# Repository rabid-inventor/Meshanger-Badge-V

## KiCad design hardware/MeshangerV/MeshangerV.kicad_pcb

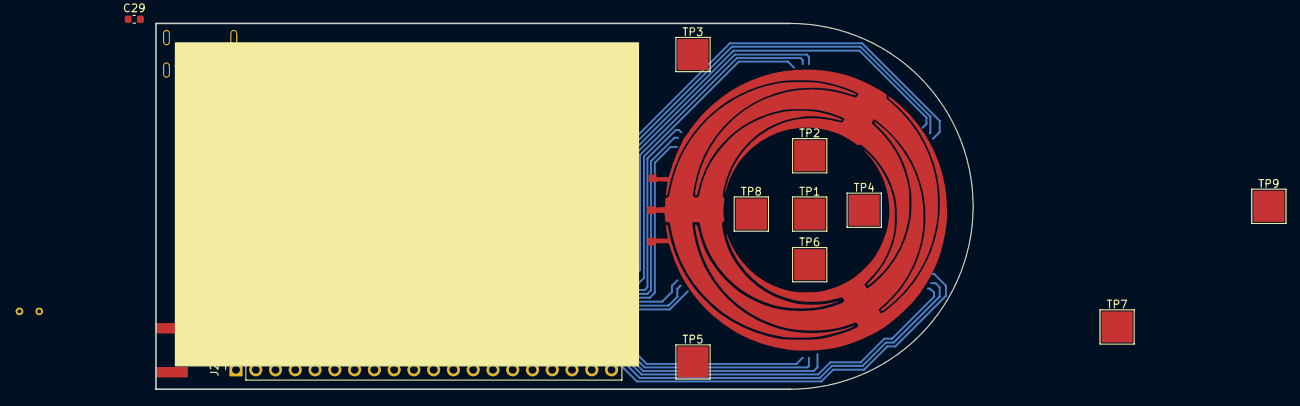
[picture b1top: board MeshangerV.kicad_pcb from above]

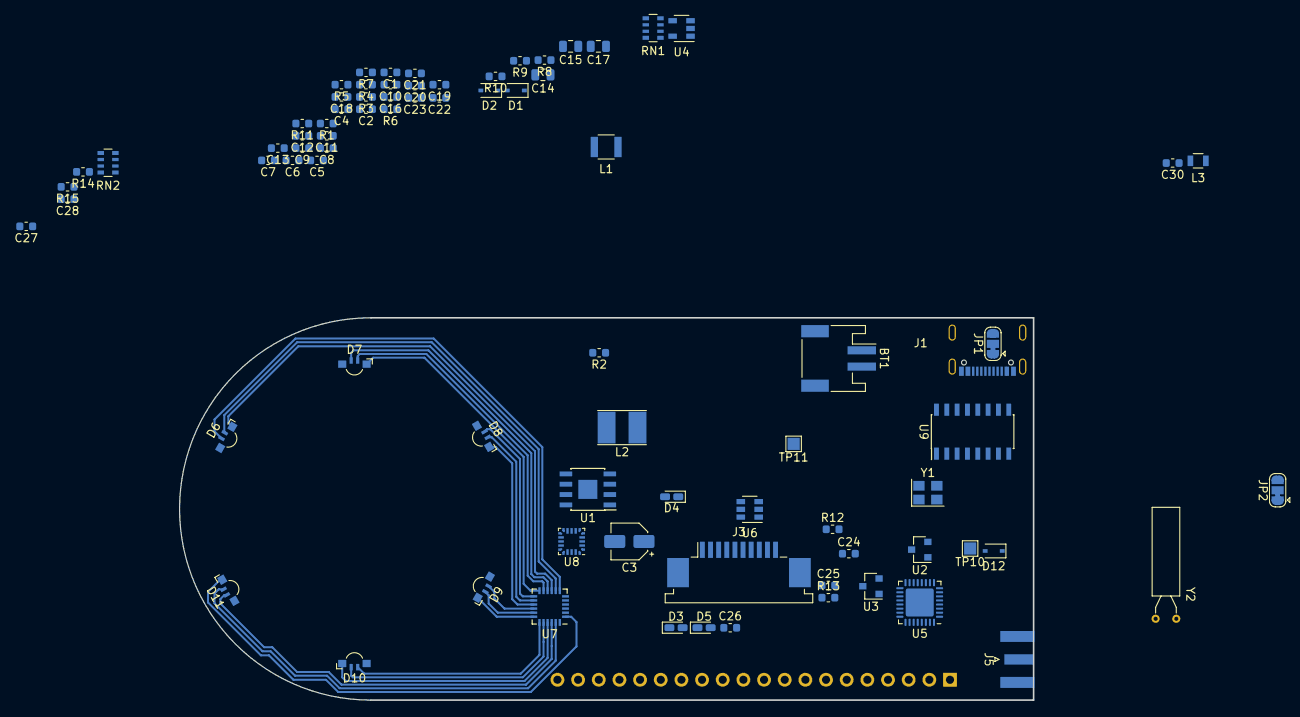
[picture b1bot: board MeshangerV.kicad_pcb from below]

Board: 2 copper layers, 105.0 x 47.0 mm, 92 parts (80 on the bottom side), 78 nets.

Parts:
BT1: Battery_Cell; JST_PH_S2B-PH-SM4-TB_02x2.00mm_Angled
C1, C2, C4, C5, C6, C7, C9, C11, C12, C13, C16, C18, C19, C20, C21, C22, C23, C24, C25, C26, C27, C28, C29, C30: C_Small; C_0603_1608Metric
C3: CP; CP_Elec_4x4.5
C8, C10: 1uF; C_0603_1608Metric
C14, C15: 22uF; C_0805_2012Metric
C17: 10uF; C_0805_2012Metric
D1, D2, D12: D_Schottky; D_SOD-323
D3, D4, D5: LED; LED_0603_1608Metric_Castellated
D6, D7, D8, D9, D10, D11: LED_RABG; LED_Kingbright_APFA3010_3x1.5mm_Horizontal
J1: USB_C_Receptacle_USB2.0; VACON_CSP_USC16_TR
J2: Conn_01x20_Male; PinSocket_1x20_P2.54mm_Vertical
J3: Conn_01x10_MountingPin; TE_1-84952-0_1x10-1MP_P1.0mm_Horizontal
J4: Conn_01x03; touchwheel
J5: Conn_Coaxial; SMA_Samtec_SMA-J-P-H-ST-EM1_EdgeMount
JP1, JP2: SolderJumper_3_Bridged12; SolderJumper-3_P1.3mm_Bridged12_RoundedPad1.0x1.5mm
L1: L_Small; L_1210
L2: L_Small; L_Taiyo-Yuden_NR-40xx_HandSoldering
L3: L_Small; L_0805
R1, R2, R3, R4, R5, R6, R7, R8, R9, R10, R11, R12, R13, R14, R15: R_Small; R_0603_1608Metric
RN1, RN2: R_Pack04; R_Array_Convex_4x0603
TP1, TP2, TP3, TP4, TP5, TP6, TP7, TP8, TP9: TestPoint; TestPoint_Pad_4.0x4.0mm
TP10: CH_BL_SEL; TestPoint_Pad_1.5x1.5mm
TP11: PROGVCC; TestPoint_Pad_1.5x1.5mm
U1: TP4056; SOIC-8-1EP_3.9x4.9mm_P1.27mm_EP2.35x2.35mm
U2, U3: AP7333-33SRG-7; SOT-23
U4: AP3012KTR-G1; SOT-23-5
U5: ESP32-C3; QFN-32-1EP_5x5mm_P0.5mm_EP3.45x3.45mm
U6: AP2502KTR-G1; SOT-23-6
U7: SN3218; QFN-24_4x4mm_Pitch0.5mm
U8: AT42QT2120; ST_UFQFPN-20_3x3mm_Pitch0.5mm
U9: CH552G; SOIC-16_3.9x9.9mm_P1.27mm
Y1: 40MHz; Crystal_SMD_Abracon_ABM8G-4Pin_3.2x2.5mm
Y2: 32k; Crystal_AT310_D3.0mm_L10.0mm_Horizontal

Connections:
+3.3VA: C10.1, C14.1, C16.1, C19.1, C22.1, J2.18, U3.2, U5.2, U5.3, U5.31, U5.32
+3V3: C3.1, C4.1, C5.1, C7.1, C8.1, C9.1, C11.1, C15.1, C17.1, C20.1, C23.1, C24.1, C27.1, C28.1, D1.1, D2.1, D3.2, D4.2, D5.2, D6.2, D7.2, D8.2, D9.2, D10.2, D11.2, D12.2, J2.17, J2.19, J3.5, R11.1, R12.1, R15.1, RN1.6, RN1.7, RN1.8, RN2.5, RN2.6, RN2.7, RN2.8, U2.2, U2.3, U3.3, U5.11, U5.17, U7.3, U8.9, U9.16
/ANT: C29.1, L3.1, U5.1
/BLSEL: J2.9, J3.8, U5.15, U9.3
/BVOLT: J2.16, R7.2, R8.1, U5.6
/CC1: J1.A5, R5.2
/CC2: J1.B5, R4.2
/CHRG_SD: R6.2, U1.8
/CHUSB+: JP2.1, TP10.1, U9.12
/CHUSB-: JP1.1, U9.13
/Display hardware/RES: J3.9, R12.2
/Display hardware/V0: C25.1, J3.3
/Display hardware/VG: C26.1, J3.1
/Display hardware/XV0: C25.2, J3.2
/ESPUSB+: J2.6, JP2.3, U5.26
/ESPUSB-: J2.5, JP1.3, U5.25
/ESP_ENABLE: R11.2, U5.7, U9.2
/ESP_RX: J2.3, U5.27, U9.7
/ESP_TX: J2.4, U5.28, U9.8
/INPUTINT: J2.10, J3.10, RN1.1, RN2.3, U5.14, U8.15
/LCD_BL_EN: J2.8, R13.1, RN1.4, U5.16, U6.1
/LED_SD: RN2.4, U7.24
/MISO: J2.12, U5.10
/MOSI: J2.13, J3.6, U5.12
/SCK: J2.11, J3.7, U5.13
/SCL: J2.14, RN2.2, U5.9, U8.14, U9.4
/SDA: J2.15, RN2.1, U5.8, U7.5, U7.6, U8.11, U9.5
/V_BAT: BT1.1, C2.1, C6.1, L2.2, R7.1, U1.5, U4.5
/_CHRG: U1.7, U9.10
/_STDBY: U1.6, U9.9
/control hardware/1B: D6.3, U7.7
/control hardware/1G: D6.4, U7.8
/control hardware/1R: D6.1, U7.9
/control hardware/2B: D7.3, U7.10
/control hardware/2G: D7.4, U7.11
/control hardware/2R: D7.1, U7.12
/control hardware/3B: D8.3, U7.13
/control hardware/3G: D8.4, U7.14
/control hardware/3R: D8.1, U7.15
/control hardware/4B: D9.3, U7.16
/control hardware/4G: D9.4, U7.17
/control hardware/4R: D9.1, U7.18
/control hardware/5B: D10.3, U7.19
/control hardware/5G: D10.4, U7.20
/control hardware/5R: D10.1, U7.21
/control hardware/6B: D11.3, U7.22
/control hardware/6G: D11.4, U7.23
/control hardware/6R: D11.1, U7.1
/control hardware/C_PAD: TP5.1, U8.20
/control hardware/DL_PAD: TP3.1, U8.18
/control hardware/DR_PAD: TP9.1, U8.16
/control hardware/D_PAD: TP6.1, U8.17
/control hardware/L_PAD: TP2.1, U8.1
/control hardware/R_PAD: TP8.1, U8.19
/control hardware/UL_PAD: TP1.1, U8.4
/control hardware/UR_PAD: TP7.1, U8.2
/control hardware/U_PAD: TP4.1, U8.3
/control hardware/WHEEL1: J4.1, U8.7
/control hardware/WHEEL2: J4.2, U8.6
/control hardware/WHEEL3: J4.3, U8.5
GND: BT1.2, C1.2, C2.2, C3.2, C4.2, C5.2, C6.2, C7.2, C8.2, C9.2, C10.2, C11.2, C12.2, C13.2, C14.2, C15.2, C16.2, C17.2, C18.2, C19.2, C20.2, C21.2, C22.2, C23.2, C24.2, C26.2, C27.2, C28.2, C29.2, C30.2, J1.A1, J1.A12, J1.B1, J1.B12, J2.1, J2.2, J3.4, J3.MP, J5.2, R1.2, R3.2, R4.1, R5.1, R8.2, R10.2, R13.2, R14.2, RN1.5, U1.3, U2.1, U3.1, U4.2, U5.33, U6.2, U8.8, U8.10, U9.14
unnamed: C12.1, U5.29, Y1.1
unnamed: C13.1, U5.30, Y1.2
unnamed: C18.1, U5.4, Y2.1
unnamed: C21.1, U5.5, Y2.2
unnamed: C30.1, J5.1, L3.2
unnamed: D1.2, L1.1
unnamed: D2.2, L2.1, R9.1, U4.1
unnamed: D3.1, D4.1, D5.1, U6.3
unnamed: D12.1, TP11.1, U9.15
unnamed: J1.A6, J1.B6, JP2.2
unnamed: J1.A7, J1.B7, JP1.2
unnamed: R1.1, U1.2
unnamed: R2.2, R3.1, U1.1
unnamed: R9.2, R10.1, U4.3
unnamed: R14.1, U7.2
unnamed: R15.2, U8.12
VBUS: C1.1, J1.A4, J1.A9, J1.B4, J1.B9, J2.20, L1.2, R2.1, R6.1, U1.4, U4.4, U9.1

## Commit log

2020-11-24 started schematic
2020-11-26 more schmatic work
2020-11-30 more schematic
2020-12-07 schematic complete more or less
2021-01-20 routing has begun
